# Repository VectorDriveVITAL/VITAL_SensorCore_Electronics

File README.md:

# [Project Name] — VITAL PCB Repository

Centralized repository for all PCB's for VECTOR Drive's PCB work.

## Boards

| Board | Function | Status |
|---|---|---|
| `CapstonePractice` | Practice board for planning around STM32C092 | Practice |
| `SensorCore_v1` | V1 of Sensor Core board | Schematic/PCB partially done |
| `SensorPack_v1` | V1 of Sensor Core board | Schematic partially done |

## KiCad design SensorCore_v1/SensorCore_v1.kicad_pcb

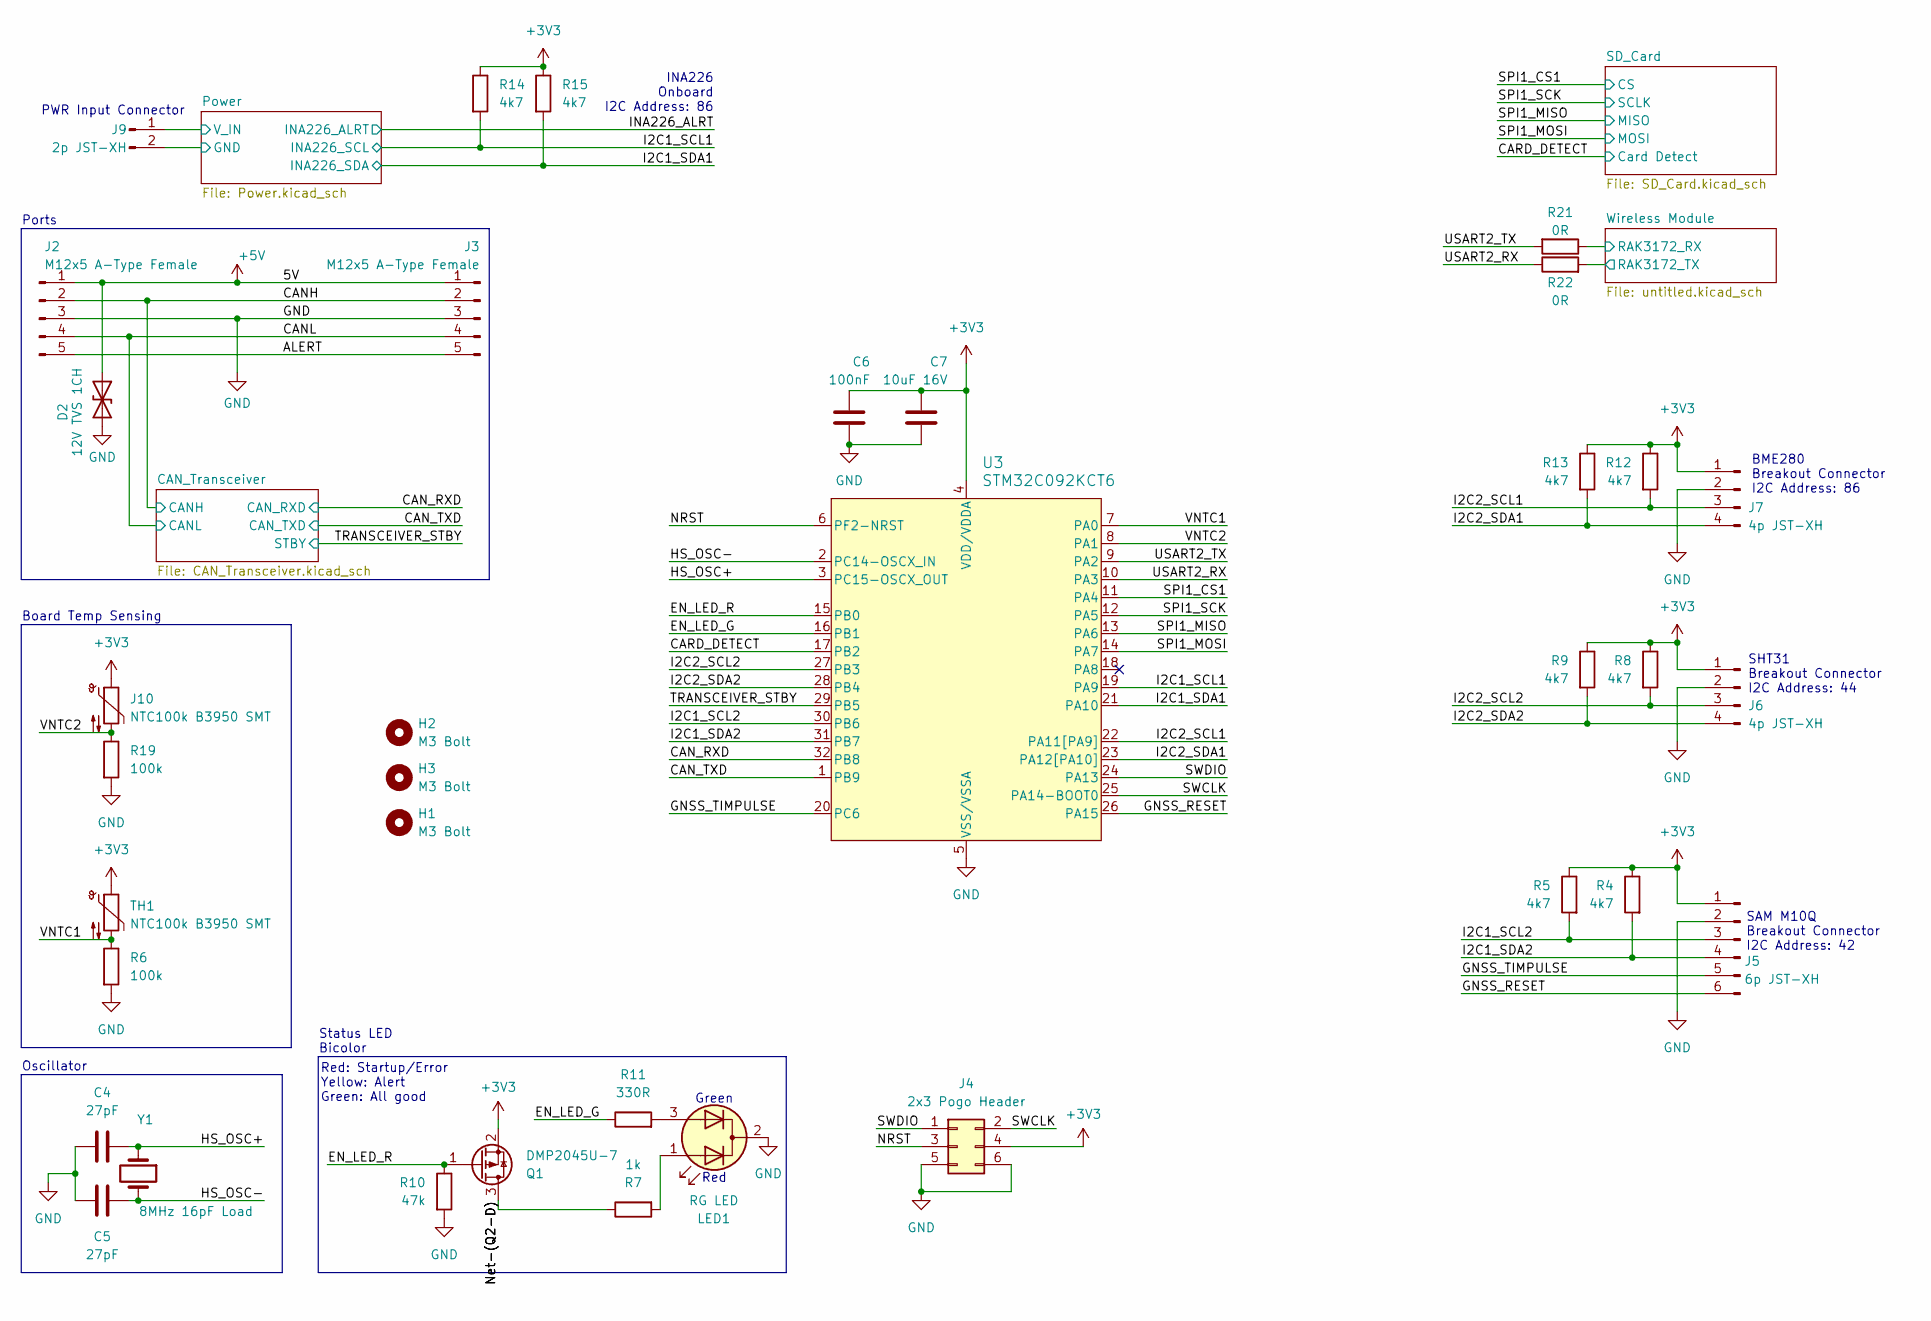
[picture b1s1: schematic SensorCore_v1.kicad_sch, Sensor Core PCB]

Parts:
C4, C5: 27pF; C_0603_1608Metric_Pad1.08x0.95mm_HandSolder; Digikey Part CL10C270JB8NNNC
C6: 100nF; C_0603_1608Metric_Pad1.08x0.95mm_HandSolder; Digikey Part CL10B104KB8NFNC
C7: 10uF 16V; C_0805_2012Metric_Pad1.18x1.45mm_HandSolder; Digikey Part CL21A106KOQNNNE
D2: 12V TVS 1CH; D_SMA; Digikey Part SMAJ6.0A-13-F
H1, H2, H3: M3 Bolt; MountingHole_3.2mm_M3
J2, J3: M12x5 A-Type Female; M12A05PFFRSF7003
J4: 2x3 Pogo Header; PinHeader_2x03_P2.54mm_Vertical
J5: 6p JST-XH; JST_XH_B6B-XH-A_1x06_P2.50mm_Vertical
J6, J7: 4p JST-XH; JST_XH_B4B-XH-A_1x04_P2.50mm_Vertical
J9: 2p JST-XH; JST_XH_B2B-XH-A_1x02_P2.50mm_Vertical
J10: NTC100k B3950 SMT; JST_XH_B2B-XH-A_1x02_P2.50mm_Vertical; Digikey Part JSNB104J395FABXG
LED1: RG LED; LED_D3.0mm-3; Digikey Part WP59SURKZGW
Q1: DMP2045U-7; SOT-23-3; Digikey Part DMP2045U-7
R4, R5: 4k7; R_0603_1608Metric_Pad0.98x0.95mm_HandSolder; Part RMCF0603FT1K00; Digikey Part RMCF0603FT4K70
R6, R19: 100k; R_0603_1608Metric_Pad0.98x0.95mm_HandSolder; Digikey Part RMCF0603FT2K20
R7: 1k; R_0603_1608Metric_Pad0.98x0.95mm_HandSolder; Digikey Part RMCF0603FT2K20
R8, R9, R12, R13, R14, R15: 4k7; R_0603_1608Metric_Pad0.98x0.95mm_HandSolder; Digikey Part RMCF0603FT4K70
R10: 47k; R_0603_1608Metric_Pad0.98x0.95mm_HandSolder; Digikey Part RMCF0603JT47K0
R11: 330R; R_0603_1608Metric_Pad0.98x0.95mm_HandSolder; Digikey Part RMCF0603FT4K70
R21, R22: 0R; R_0603_1608Metric_Pad0.98x0.95mm_HandSolder; Digikey Part RMCF0603FT4K70
TH1: NTC100k B3950 SMT; R_0603_1608Metric_Pad0.98x0.95mm_HandSolder; Digikey Part JSNB104J395FABXG
U3: STM32C092KCT6; LQFP-32_7x7mm_P0.8mm; Digikey Part STM32C092KCT6
Y1: 8MHz 16pF Load; Crystal_6x3.5mm; Digikey Part ABM3-8.000MHZ-D2Y-T

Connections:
+3V3: C6.2, C7.1, J4.4, J5.1, J6.1, J7.1, J10.1, Q1.2 (S), R4.1, R5.1, R8.1, R9.1, R12.1, R13.1, R14.1, R15.1, TH1.1, U3.4 (VDD/VDDA); also elsewhere on the board
+5V: D2.1 (A1), J2.1, J3.1; also elsewhere on the board
/ALERT: J2.5, J3.5
/CANH: J2.2, J3.2; also elsewhere on the board
/CANL: J2.4, J3.4; also elsewhere on the board
/CAN_RXD: U3.32 (PB8); also elsewhere on the board
/CAN_TXD: U3.1 (PB9); also elsewhere on the board
/CARD_DETECT: U3.17 (PB2); also elsewhere on the board
/EN_LED_G: R11.1, U3.16 (PB1)
/EN_LED_R: Q1.1 (G), R10.1, U3.15 (PB0)
/GNSS_RESET: J5.6, U3.26 (PA15)
/GNSS_TIMPULSE: J5.5, U3.20 (PC6)
/HS_OSC+: C4.1, U3.3 (PC15-OSCX_OUT), Y1.1
/HS_OSC-: C5.1, U3.2 (PC14-OSCX_IN), Y1.2
/I2C1_SCL1: R14.2, U3.19 (PA9); also elsewhere on the board
/I2C1_SCL2: J5.3, R5.2, U3.30 (PB6)
/I2C1_SDA1: R15.2, U3.21 (PA10); also elsewhere on the board
/I2C1_SDA2: J5.4, R4.2, U3.31 (PB7)
/I2C2_SCL1: J7.3, R12.2, U3.22 (PA11[PA9])
/I2C2_SCL2: J6.3, R8.2, U3.27 (PB3)
/I2C2_SDA1: J7.4, R13.2, U3.23 (PA12[PA10])
/I2C2_SDA2: J6.4, R9.2, U3.28 (PB4)
/NRST: J4.3, U3.6 (PF2-NRST)
/Net-(Q2-D): Q1.3 (D), R7.1
/SPI1_CS1: U3.11 (PA4); also elsewhere on the board
/SPI1_MISO: U3.13 (PA6); also elsewhere on the board
/SPI1_MOSI: U3.14 (PA7); also elsewhere on the board
/SPI1_SCK: U3.12 (PA5); also elsewhere on the board
/SWCLK: J4.2, U3.25 (PA14-BOOT0)
/SWDIO: J4.1, U3.24 (PA13)
/TRANSCEIVER_STBY: U3.29 (PB5); also elsewhere on the board
/USART2_RX: R22.1, U3.10 (PA3)
/USART2_TX: R21.2, U3.9 (PA2)
/VNTC1: R6.1, TH1.2, U3.7 (PA0)
/VNTC2: J10.2, R19.1, U3.8 (PA1)
/Wireless Module/RAK3172_RX: R21.1; also elsewhere on the board
/Wireless Module/RAK3172_TX: R22.2; also elsewhere on the board
GND: C4.2, C5.2, C6.1, C7.2, D2.2 (A2), J2.3, J3.3, J4.5, J4.6, J5.2, J6.2, J7.2, J9.2, LED1.2 (K), R6.2, R10.2, R19.2, U3.5 (VSS/VSSA); also elsewhere on the board
unnamed: LED1.1 (A1), R7.2
unnamed: LED1.3 (A2), R11.2
VBat_in: J9.1; also elsewhere on the board

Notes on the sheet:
Board Temp Sensing
SHT31 Breakout Connector I2C Address: 44
Oscillator
Red
Status LED Bicolor
INA226 Onboard I2C Address: 86
BME280 Breakout Connector I2C Address: 86
PWR Input Connector
Ports
Green
Red: Startup/Error Yellow: Alert Green: All good
SAM M10Q Breakout Connector I2C Address: 42

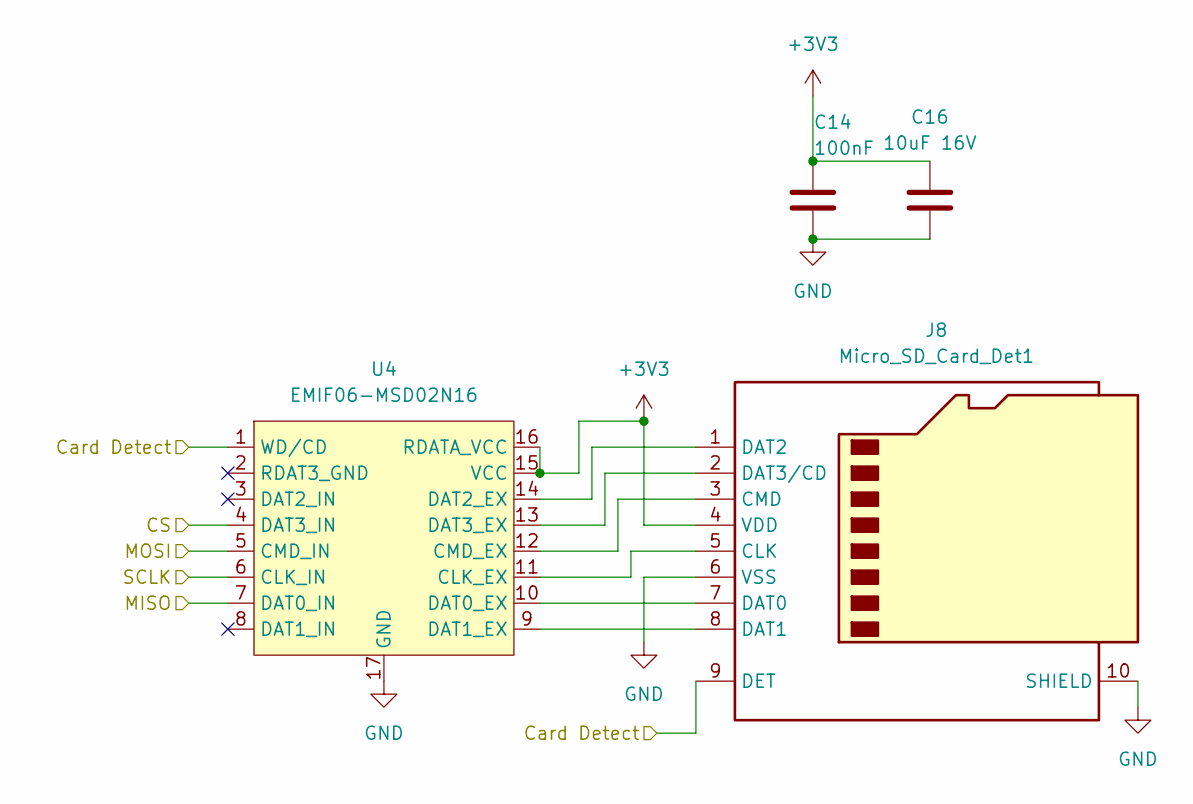
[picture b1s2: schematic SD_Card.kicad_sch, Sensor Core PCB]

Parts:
C14: 100nF; C_0603_1608Metric_Pad1.08x0.95mm_HandSolder; Digikey Part CL10B104KB8NFNC
C16: 10uF 16V; C_0805_2012Metric_Pad1.18x1.45mm_HandSolder; Digikey Part CL21A106KOQNNNE
J8: Micro_SD_Card_Det1; CUI_MSD-11-A; Digikey Part MSD-11-A
U4: EMIF06-MSD02N16; OnSemi_UDFN-16-1EP_1.35x3.3mm_P0.4mm_EP0.4x2.8mm; Digikey Part EMIF06-MSD02N16

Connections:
+3V3: C14.2, C16.1, J8.4 (VDD), U4.15 (VCC), U4.16 (RDATA_VCC); also elsewhere on the board
/CARD_DETECT: J8.9 (DET), U4.1 (WD/CD); also elsewhere on the board
/SPI1_CS1: U4.4 (DAT3_IN); also elsewhere on the board
/SPI1_MISO: U4.7 (DAT0_IN); also elsewhere on the board
/SPI1_MOSI: U4.5 (CMD_IN); also elsewhere on the board
/SPI1_SCK: U4.6 (CLK_IN); also elsewhere on the board
GND: C14.1, C16.2, J8.6 (VSS), J8.10 (SHIELD), U4.17 (GND); also elsewhere on the board
unnamed: J8.5 (CLK), U4.11 (CLK_EX)
unnamed: J8.3 (CMD), U4.12 (CMD_EX)
unnamed: J8.7 (DAT0), U4.10 (DAT0_EX)
unnamed: J8.8 (DAT1), U4.9 (DAT1_EX)
unnamed: J8.1 (DAT2), U4.14 (DAT2_EX)
unnamed: J8.2 (DAT3/CD), U4.13 (DAT3_EX)

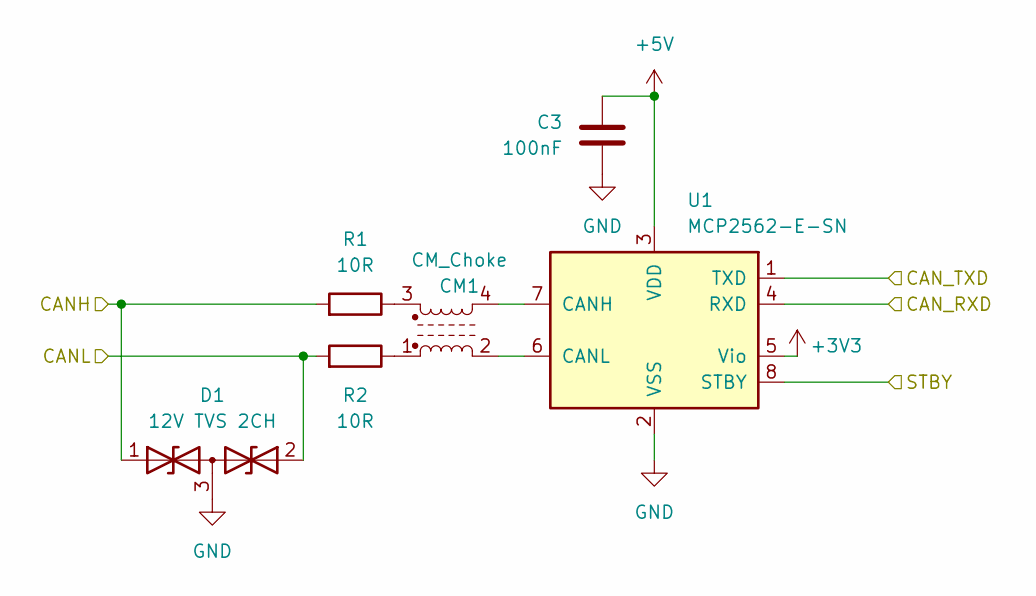
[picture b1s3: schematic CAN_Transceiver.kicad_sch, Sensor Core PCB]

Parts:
C3: 100nF; C_0603_1608Metric_Pad1.08x0.95mm_HandSolder; Digikey Part CL10B104KB8NFNC
CM1: CM_Choke; CMChoke_2.6x1.2mm_HandSolder; Digikey Part SCM2012FS181MDG
D1: 12V TVS 2CH; SOT-23-3; Digikey Part DESD12VL2BTQ-7
R1, R2: 10R; R_0603_1608Metric_Pad0.98x0.95mm_HandSolder
U1: MCP2562-E-SN; SOIC-8_3.9x4.9mm_P1.27mm; Digikey Part MCP2562-E-SN

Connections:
+3V3: U1.5 (Vio); also elsewhere on the board
+5V: C3.1, U1.3 (VDD); also elsewhere on the board
/CANH: D1.1 (A1), R1.2; also elsewhere on the board
/CANL: D1.2 (A2), R2.2; also elsewhere on the board
/CAN_RXD: U1.4 (RXD); also elsewhere on the board
/CAN_TXD: U1.1 (TXD); also elsewhere on the board
/TRANSCEIVER_STBY: U1.8 (STBY); also elsewhere on the board
GND: C3.2, D1.3 (common), U1.2 (VSS); also elsewhere on the board
unnamed: CM1.1, R2.1
unnamed: CM1.3, R1.1
unnamed: CM1.4, U1.7 (CANH)
unnamed: CM1.2, U1.6 (CANL)

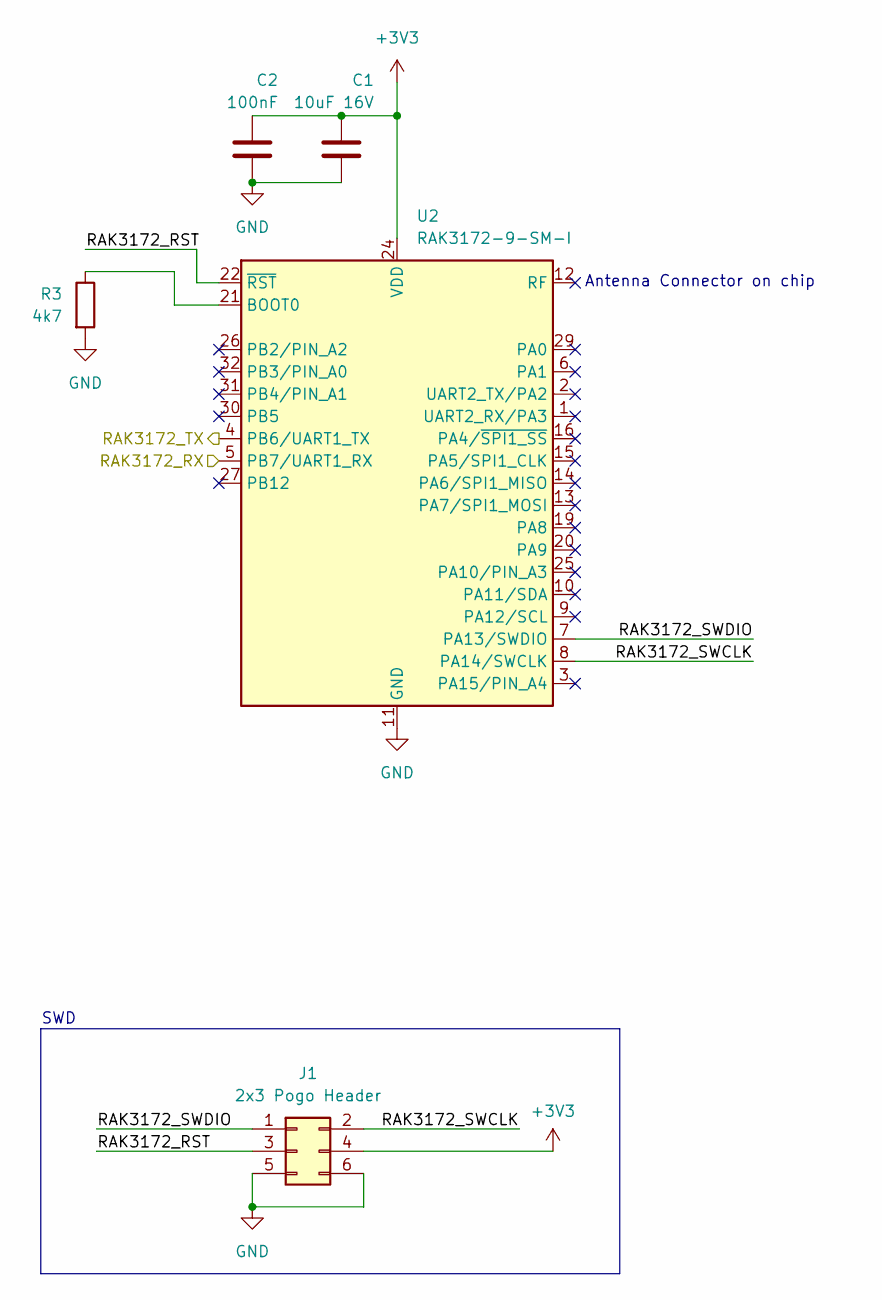
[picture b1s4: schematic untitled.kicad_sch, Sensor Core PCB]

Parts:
C1: 10uF 16V; C_0805_2012Metric_Pad1.18x1.45mm_HandSolder; Digikey Part CL21A106KOQNNNE
C2: 100nF; C_0603_1608Metric_Pad1.08x0.95mm_HandSolder; Digikey Part CL10B104KB8NFNC
J1: 2x3 Pogo Header; PinHeader_2x03_P2.54mm_Vertical
R3: 4k7; R_0603_1608Metric_Pad0.98x0.95mm_HandSolder; Digikey Part RMCF0603FT4K70
U2: RAK3172-9-SM-I; RAK3172; Digikey Part RAK3172-9-SM-I

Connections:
+3V3: C1.1, C2.2, J1.4, U2.24 (VDD); also elsewhere on the board
/Wireless Module/RAK3172_RST: J1.3, U2.22 (~RST)
/Wireless Module/RAK3172_RX: U2.5 (PB7/UART1_RX); also elsewhere on the board
/Wireless Module/RAK3172_SWCLK: J1.2, U2.8 (PA14/SWCLK)
/Wireless Module/RAK3172_SWDIO: J1.1, U2.7 (PA13/SWDIO)
/Wireless Module/RAK3172_TX: U2.4 (PB6/UART1_TX); also elsewhere on the board
GND: C1.2, C2.1, J1.5, J1.6, R3.2, U2.11 (GND), U2.17 (GND), U2.18 (GND), U2.23 (GND), U2.28 (GND); also elsewhere on the board
unnamed: R3.1, U2.21 (BOOT0)

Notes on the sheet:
Antenna Connector on chip
SWD

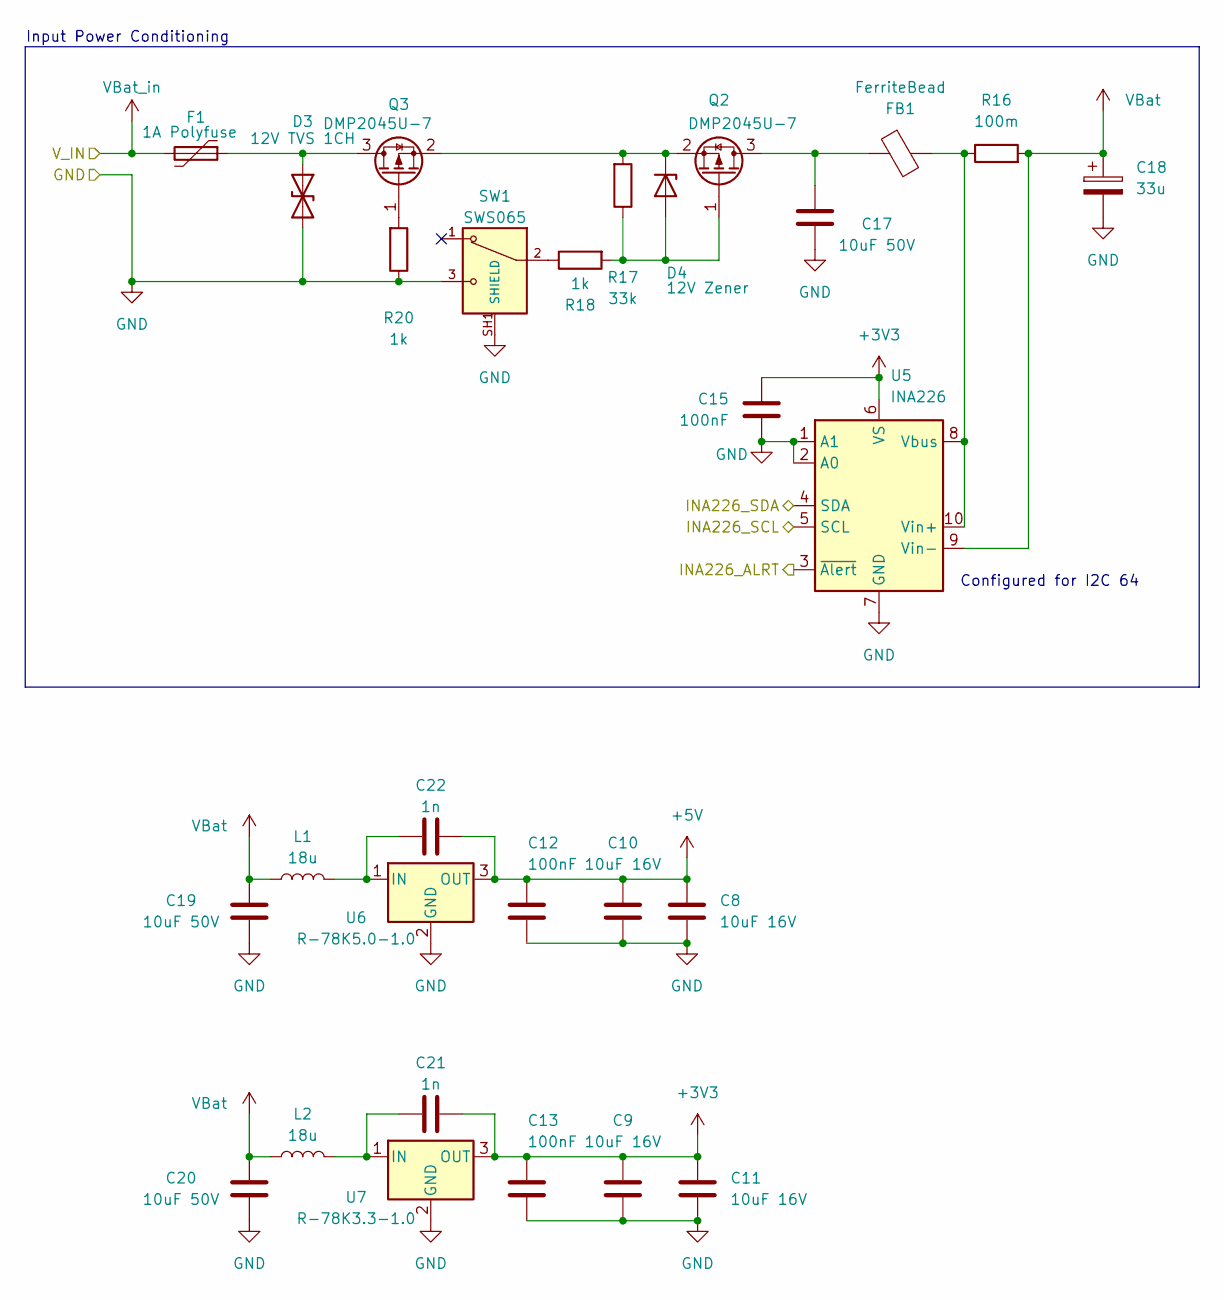
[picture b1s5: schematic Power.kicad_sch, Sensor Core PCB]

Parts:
C8, C9, C10, C11: 10uF 16V; C_0805_2012Metric_Pad1.18x1.45mm_HandSolder; Digikey Part CL21A106KOQNNNE
C12, C13, C15: 100nF; C_0603_1608Metric_Pad1.08x0.95mm_HandSolder; Digikey Part CL10B104KB8NFNC
C17, C19, C20: 10uF 50V; C_0805_2012Metric_Pad1.18x1.45mm_HandSolder; Digikey Part CL21A106KOQNNNE
C18: 33u; CP_Radial_D6.3mm_P2.50mm
C21, C22: 1n; C_0603_1608Metric_Pad1.08x0.95mm_HandSolder; Digikey Part CL10B104KB8NFNC
D3: 12V TVS 1CH; D_SMA; Digikey Part SMAJ6.0A-13-F
D4: 12V Zener; D_SOD-123
F1: 1A Polyfuse; R_1206_3216Metric_Pad1.30x1.75mm_HandSolder
FB1: FerriteBead; R_0603_1608Metric_Pad0.98x0.95mm_HandSolder; Digikey Part MPZ1608S101ATAH0
L1, L2: 18u; IFSC2020DEER5R6M01; Digikey Part IFSC2020DEER5R6M01
Q2, Q3: DMP2045U-7; SOT-23-3; Digikey Part DMP2045U-7
R16: 100m; R_0805_2012Metric_Pad1.20x1.40mm_HandSolder; Digikey Part CSR0805FKR100
R17: 33k; R_0603_1608Metric_Pad0.98x0.95mm_HandSolder; Digikey Part RMCF0603FT2K20
R18, R20: 1k; R_0603_1608Metric_Pad0.98x0.95mm_HandSolder; Digikey Part RMCF0603FT2K20
SW1: SWS065; SW_SWS065-030V12TSK_REVA; PARTREV A
U5: INA226; TSSOP-10_3x3mm_P0.5mm; Digikey Part INA226
U6: R-78K5.0-1.0; Converter_DCDC_RECOM_R-78E-0.5_THT; Digikey Part R-78K5.0-1.0
U7: R-78K3.3-1.0; Converter_DCDC_RECOM_R-78E-0.5_THT; Digikey Part R-78K3.3-1.0

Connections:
+3V3: C9.1, C11.1, C13.2, C15.2, C21.1, U5.6 (VS), U7.3 (OUT); also elsewhere on the board
+5V: C8.1, C10.1, C12.2, C22.1, U6.3 (OUT); also elsewhere on the board
/I2C1_SCL1: U5.5 (SCL); also elsewhere on the board
/I2C1_SDA1: U5.4 (SDA); also elsewhere on the board
/INA226_ALRT: U5.3 (~Alert)
GND: C8.2, C9.2, C10.2, C11.2, C12.1, C13.1, C15.1, C17.2, C18.2, C19.2, C20.2, D3.2 (A2), R20.1, SW1.3, SW1.SH1 (SHIELD), SW1.SH2 (SHIELD__1), U5.1 (A1), U5.2 (A0), U5.7 (GND), U6.2 (GND), U7.2 (GND); also elsewhere on the board
unnamed: D3.1 (A1), F1.1, Q3.3 (D)
unnamed: D4.2 (A), Q2.1 (G), R17.1, R18.2
unnamed: D4.1 (K), Q2.2 (S), Q3.2 (S), R17.2
unnamed: C17.1, FB1.1, Q2.3 (D)
unnamed: Q3.1 (G), R20.2
unnamed: R18.1, SW1.2
unnamed: FB1.2, R16.1, U5.8 (Vbus), U5.10 (Vin+)
unnamed: C22.2, L1.2, U6.1 (IN)
unnamed: C21.2, L2.2, U7.1 (IN)
VBat: C18.1, C19.1, C20.1, L1.1, L2.1, R16.2, U5.9 (Vin-)
VBat_in: F1.2; also elsewhere on the board

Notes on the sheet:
Configured for I2C 64
Input Power Conditioning

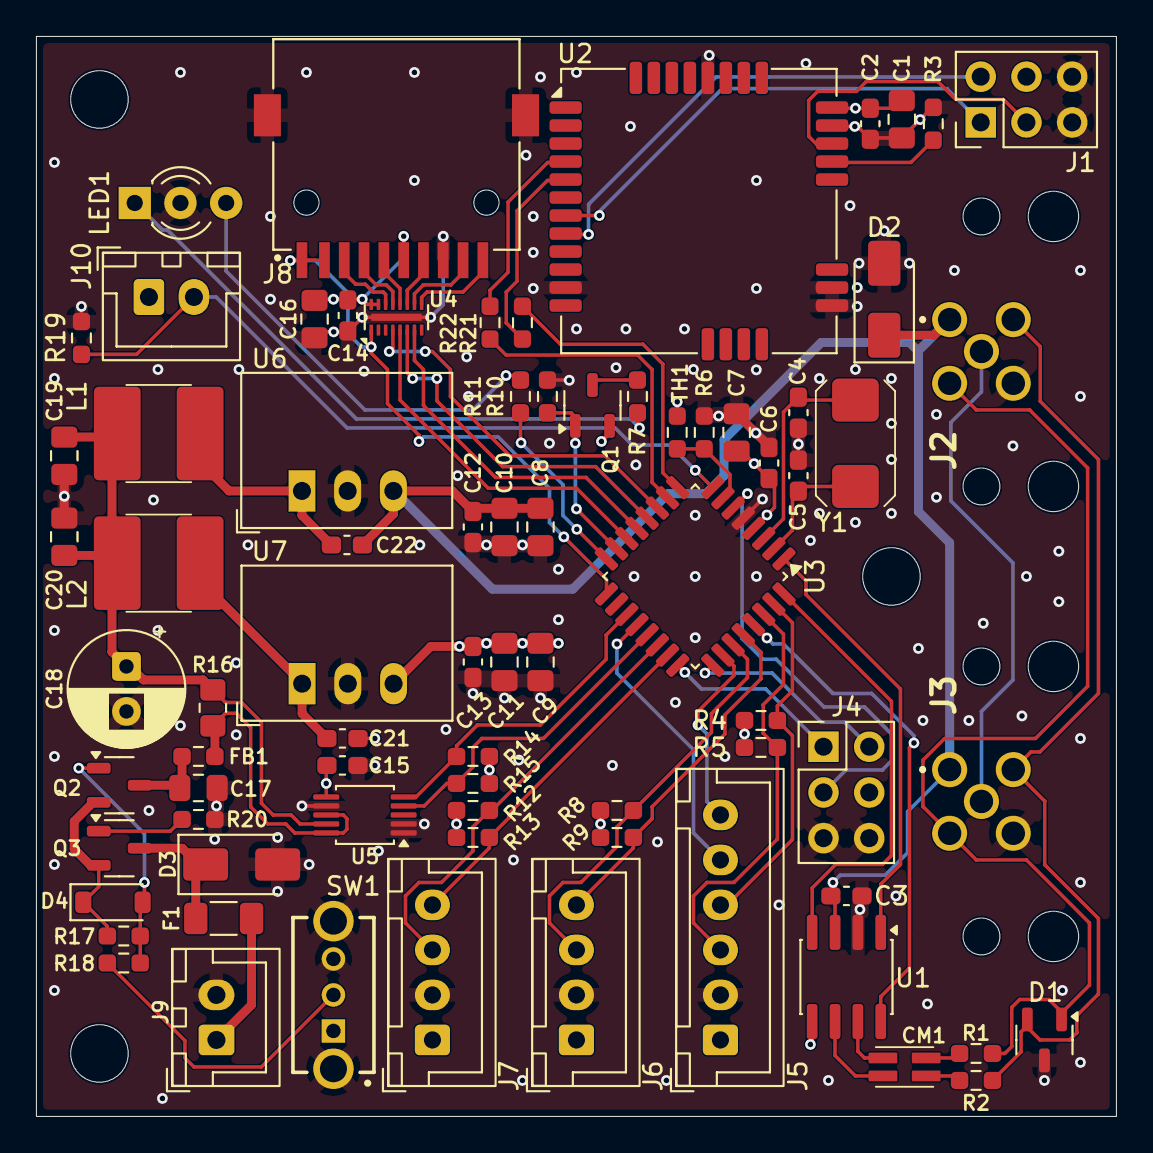
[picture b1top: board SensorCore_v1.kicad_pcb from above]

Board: 4 copper layers, 60.0 x 60.0 mm, 80 parts (0 on the bottom side), 65 nets.

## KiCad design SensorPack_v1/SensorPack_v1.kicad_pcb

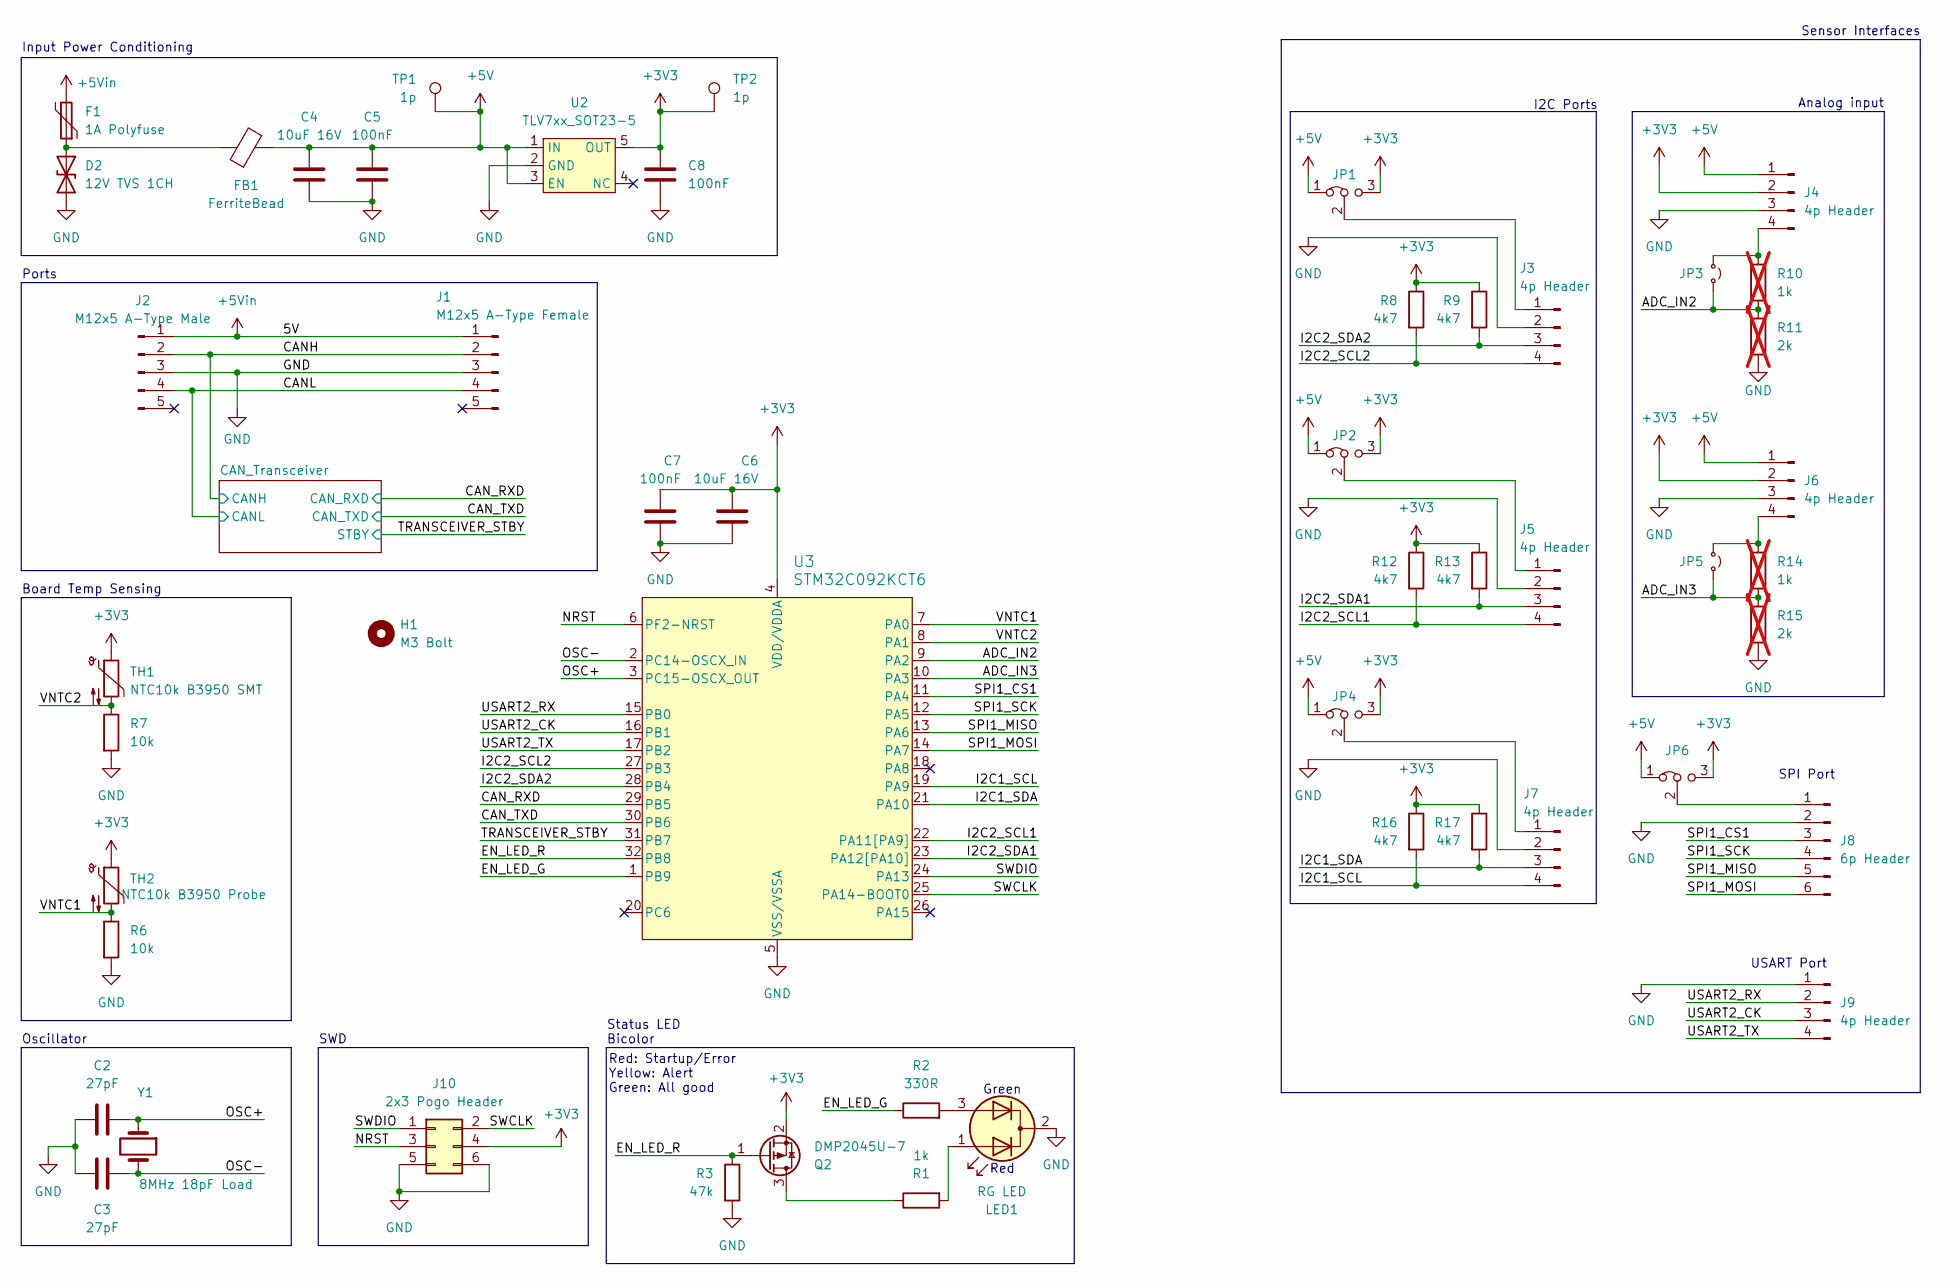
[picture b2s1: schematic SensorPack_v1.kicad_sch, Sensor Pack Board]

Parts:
C2, C3: 27pF; C_0603_1608Metric_Pad1.08x0.95mm_HandSolder; Digikey Part CL10C270JB8NNNC
C4, C6: 10uF 16V; C_0805_2012Metric_Pad1.18x1.45mm_HandSolder; Digikey Part CL21A106KPCLQNC
C5, C7, C8: 100nF; R_0603_1608Metric_Pad0.98x0.95mm_HandSolder; Digikey Part CL10B104KO8NNNC
D2: 12V TVS 1CH; D_SMA; Digikey Part SMAJ6.0A-13-F
F1: 1A Polyfuse; R_1206_3216Metric_Pad1.30x1.75mm_HandSolder; Digikey Part MF-NSMF050-2
FB1: FerriteBead; R_0603_1608Metric_Pad0.98x0.95mm_HandSolder; Digikey Part MPZ1608S101ATAH0
H1: M3 Bolt; MountingHole_3.2mm_M3
J1: M12x5 A-Type Female; M12A05PFFRSF7003; Digikey Part M12A05PFFRSF7003
J2: M12x5 A-Type Male; M12A05PMMRSF7003; Digikey Part M12A05PMMRSF7003
J3, J4, J5, J6, J7, J9: 4p Header; PinHeader_1x04_P2.54mm_Vertical
J8: 6p Header; PinHeader_1x06_P2.54mm_Vertical
J10: 2x3 Pogo Header; PinHeader_2x03_P2.54mm_Vertical
JP1, JP2, JP4, JP6: Jumper_3_Bridged12; Jumper_0603_2pos; Digikey Part RMCF0603ZT0R00
JP3, JP5: Jumper_2_Small_Open; R_0603_1608Metric_Pad0.98x0.95mm_HandSolder; Digikey Part RMCF0603ZT0R00
LED1: RG LED; LED_D3.0mm-3; Digikey Part WP59SURKZGW
Q2: DMP2045U-7; SOT-23-3; Digikey Part DMP2045U-7
R1: 1k; R_0603_1608Metric_Pad0.98x0.95mm_HandSolder; Digikey Part RMCF0603FT2K20
R2: 330R; R_0603_1608Metric_Pad0.98x0.95mm_HandSolder; Digikey Part RMCF0603FT4K70
R3: 47k; R_0603_1608Metric_Pad0.98x0.95mm_HandSolder; Digikey Part RMCF0603JT47K0
R6, R7: 10k; R_0603_1608Metric_Pad0.98x0.95mm_HandSolder; Digikey Part RMCF0603FT10K0
R8, R9, R12, R13, R16, R17: 4k7; R_0603_1608Metric_Pad0.98x0.95mm_HandSolder; Digikey Part RMCF0603FT4K70
R10, R14: 1k; R_0603_1608Metric_Pad0.98x0.95mm_HandSolder; Digikey Part RMCF0603FT1K00; not fitted
R11, R15: 2k; R_0603_1608Metric_Pad0.98x0.95mm_HandSolder; Digikey Part RMCF0603FT2K00; not fitted
TH1: NTC10k B3950 SMT; R_0603_1608Metric_Pad0.98x0.95mm_HandSolder; Digikey Part JSNB104J395FABXG
TH2: NTC10k B3950 Probe; PinHeader_1x02_P2.54mm_Vertical
TP1, TP2: 1p; PinHeader_1x01_P2.54mm_Vertical
U2: TLV7xx_SOT23-5; SOT-23-5; Digikey Part TLV75533PDBVR
U3: STM32C092KCT6; LQFP-32_7x7mm_P0.8mm; Digikey Part STM32C092KCT6
Y1: 8MHz 18pF Load; Crystal_6x3.5mm; Digikey Part ABM3-8.000MHZ-D2Y-T

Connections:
+3V3: C6.1, C7.2, C8.2, J4.2, J6.2, J10.4, JP1.3 (B), JP2.3 (B), JP4.3 (B), JP6.3 (B), Q2.2 (S), R8.1, R9.1, R12.1, R13.1, R16.1, R17.1, TH1.1, TH2.1, TP2.1 (1_1), U2.5 (OUT), U3.4 (VDD/VDDA); also elsewhere on the board
+5V: C4.1, C5.2, FB1.2, J4.1, J6.1, JP1.1 (A), JP2.1 (A), JP4.1 (A), JP6.1 (A), TP1.1 (1_1), U2.1 (IN), U2.3 (EN); also elsewhere on the board
+5Vin: F1.2, J1.1, J2.1
/ADC_IN2: JP3.2 (B), R10.2, R11.1, U3.9 (PA2)
/ADC_IN3: JP5.2 (B), R14.2, R15.1, U3.10 (PA3)
/CANH: J1.2, J2.2; also elsewhere on the board
/CANL: J1.4, J2.4; also elsewhere on the board
/CAN_RXD: U3.29 (PB5); also elsewhere on the board
/CAN_TXD: U3.30 (PB6); also elsewhere on the board
/EN_LED_G: R2.1, U3.1 (PB9)
/EN_LED_R: Q2.1 (G), R3.1, U3.32 (PB8)
/I2C1_SCL: J7.4, R16.2, U3.19 (PA9)
/I2C1_SDA: J7.3, R17.2, U3.21 (PA10)
/I2C2_SCL1: J5.4, R12.2, U3.22 (PA11[PA9])
/I2C2_SCL2: J3.4, R8.2, U3.27 (PB3)
/I2C2_SDA1: J5.3, R13.2, U3.23 (PA12[PA10])
/I2C2_SDA2: J3.3, R9.2, U3.28 (PB4)
/NRST: J10.3, U3.6 (PF2-NRST)
/OSC+: C2.1, U3.3 (PC15-OSCX_OUT), Y1.1
/OSC-: C3.1, U3.2 (PC14-OSCX_IN), Y1.2
/SPI1_CS1: J8.3, U3.11 (PA4)
/SPI1_MISO: J8.5, U3.13 (PA6)
/SPI1_MOSI: J8.6, U3.14 (PA7)
/SPI1_SCK: J8.4, U3.12 (PA5)
/SWCLK: J10.2, U3.25 (PA14-BOOT0)
/SWDIO: J10.1, U3.24 (PA13)
/TRANSCEIVER_STBY: U3.31 (PB7); also elsewhere on the board
/USART2_CK: J9.3, U3.16 (PB1)
/USART2_RX: J9.2, U3.15 (PB0)
/USART2_TX: J9.4, U3.17 (PB2)
/VNTC1: R6.1, TH2.2, U3.7 (PA0)
/VNTC2: R7.1, TH1.2, U3.8 (PA1)
GND: C2.2, C3.2, C4.2, C5.1, C6.2, C7.1, C8.1, D2.2 (A2), J1.3, J2.3, J3.2, J4.3, J5.2, J6.3, J7.2, J8.2, J9.1, J10.5, J10.6, LED1.2 (K), R3.2, R6.2, R7.2, R11.2, R15.2, U2.2 (GND), U3.5 (VSS/VSSA); also elsewhere on the board
unnamed: D2.1 (A1), F1.1, FB1.1
unnamed: J3.1, JP1.2 (C)
unnamed: J4.4, JP3.1 (A), R10.1
unnamed: J5.1, JP2.2 (C)
unnamed: J6.4, JP5.1 (A), R14.1
unnamed: J7.1, JP4.2 (C)
unnamed: J8.1, JP6.2 (C)
unnamed: LED1.1 (A1), R1.2
unnamed: LED1.3 (A2), R2.2
unnamed: Q2.3 (D), R1.1

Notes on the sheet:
Board Temp Sensing
Oscillator
Red
Analog input
SPI Port
SWD
I2C Ports
USART Port
Red: Startup/Error Yellow: Alert Green: All good
Sensor Interfaces
Ports
Input Power Conditioning
Status LED Bicolor
Green

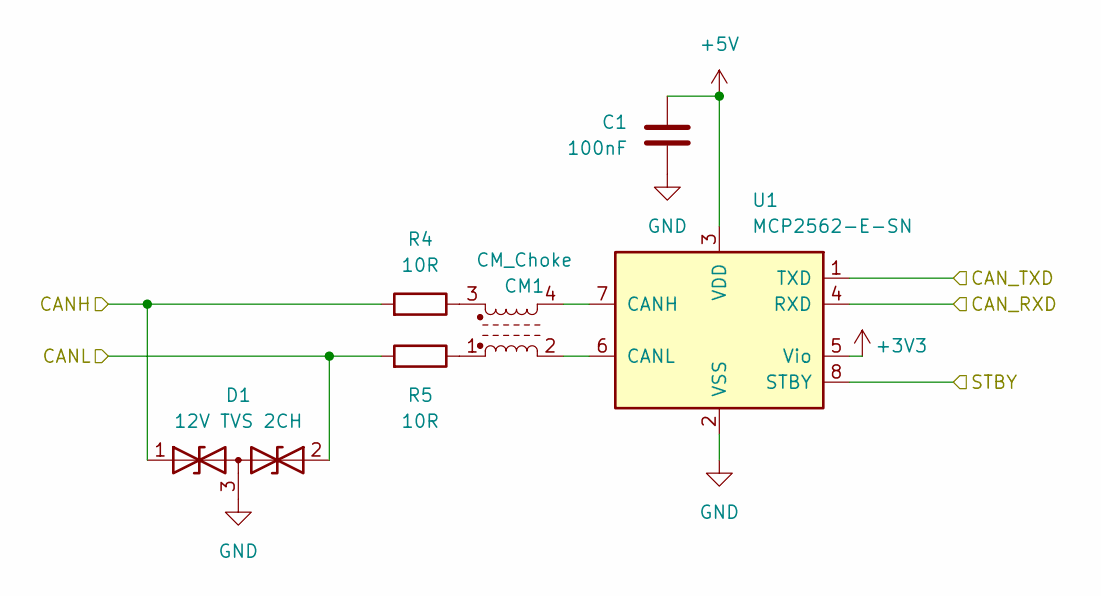
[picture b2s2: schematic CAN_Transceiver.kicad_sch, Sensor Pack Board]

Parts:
C1: 100nF; R_0603_1608Metric_Pad0.98x0.95mm_HandSolder; Digikey Part CL10B104KO8NNNC
CM1: CM_Choke; CMChoke_2.6x1.2mm_HandSolder; Digikey Part SCM2012FS181MDG
D1: 12V TVS 2CH; SOT-23-3; Digikey Part DESD15VL2BTQ-7
R4, R5: 10R; R_0603_1608Metric_Pad0.98x0.95mm_HandSolder; Digikey Part RMCF0603FT10R0
U1: MCP2562-E-SN; SOIC-8_3.9x4.9mm_P1.27mm; Digikey Part MCP2562-E/SN

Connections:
+3V3: U1.5 (Vio); also elsewhere on the board
+5V: C1.1, U1.3 (VDD); also elsewhere on the board
/CANH: D1.1 (A1), R4.2; also elsewhere on the board
/CANL: D1.2 (A2), R5.2; also elsewhere on the board
/CAN_RXD: U1.4 (RXD); also elsewhere on the board
/CAN_TXD: U1.1 (TXD); also elsewhere on the board
/TRANSCEIVER_STBY: U1.8 (STBY); also elsewhere on the board
GND: C1.2, D1.3 (common), U1.2 (VSS); also elsewhere on the board
unnamed: CM1.1, R5.1
unnamed: CM1.3, R4.1
unnamed: CM1.4, U1.7 (CANH)
unnamed: CM1.2, U1.6 (CANL)

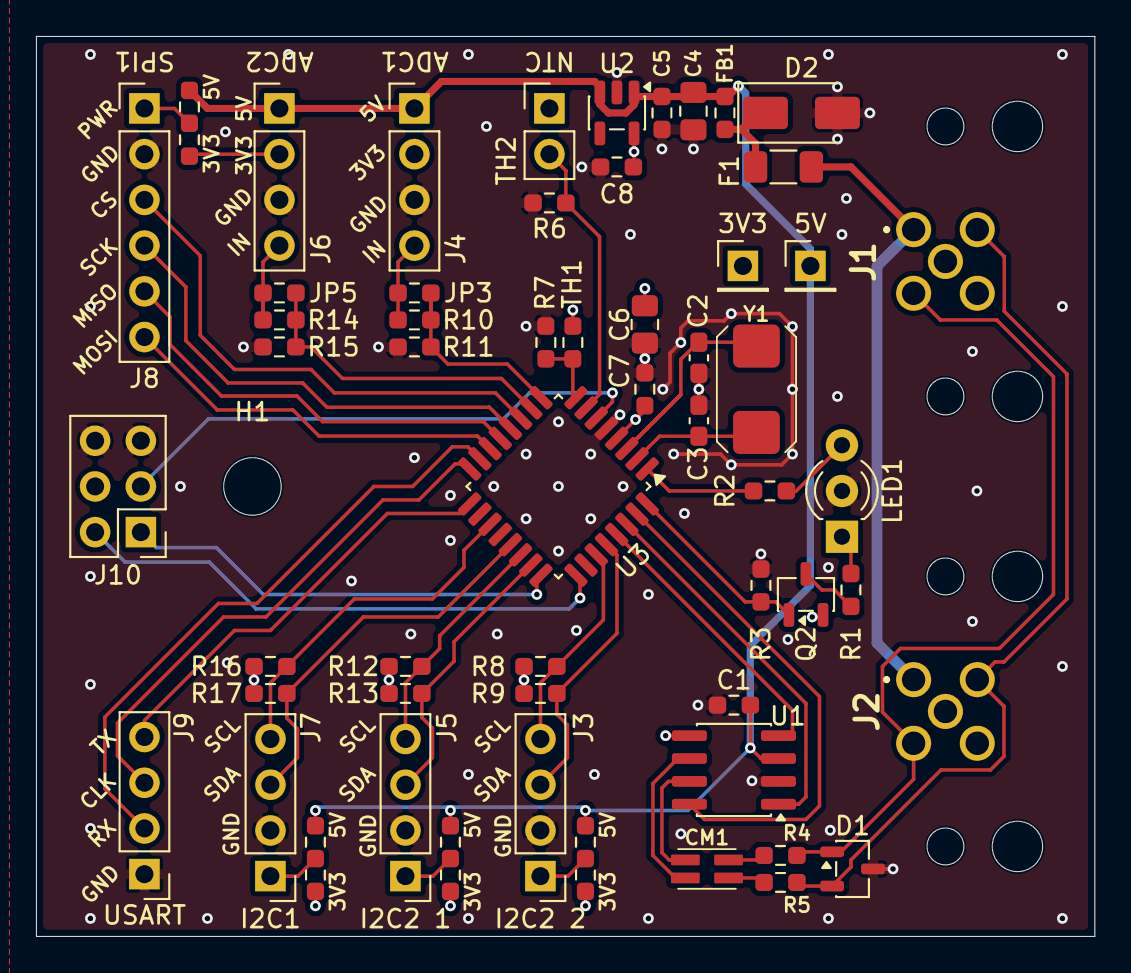
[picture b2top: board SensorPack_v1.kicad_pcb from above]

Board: 4 copper layers, 58.8 x 50.0 mm, 57 parts (0 on the bottom side), 47 nets.
